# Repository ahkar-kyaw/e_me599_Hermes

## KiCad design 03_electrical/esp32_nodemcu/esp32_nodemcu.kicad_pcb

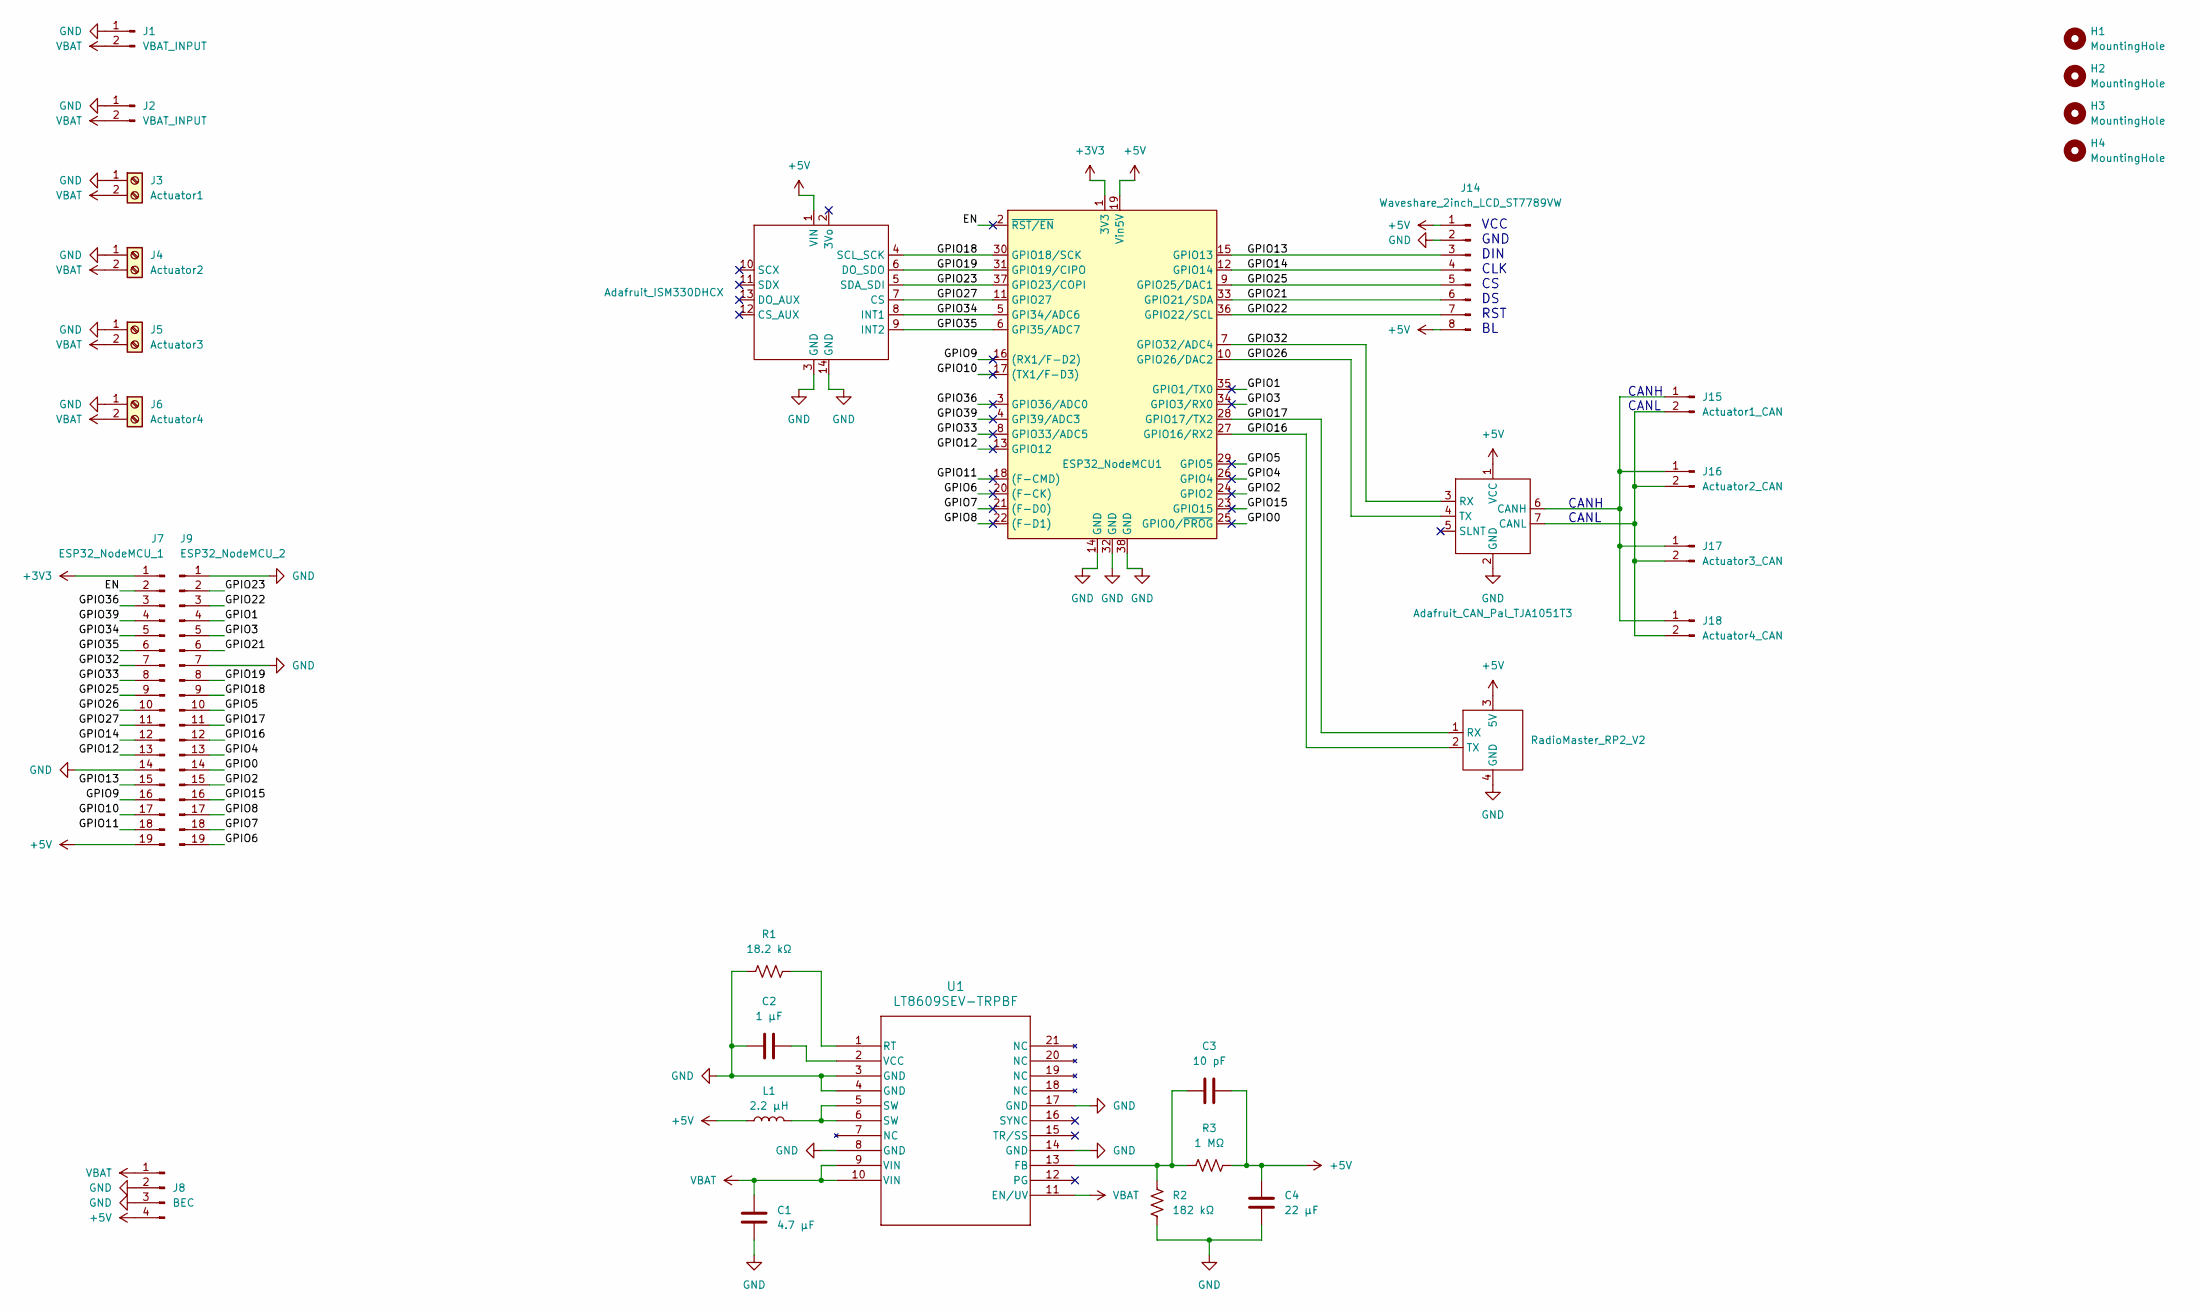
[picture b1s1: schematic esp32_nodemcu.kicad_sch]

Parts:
A1: Adafruit_ISM330DHCX
A2: Adafruit_CAN_Pal_TJA1051T3
A3: RadioMaster_RP2_V2
C1: 4.7 μF; C_1206_3216Metric_Pad1.33x1.80mm_HandSolder
C2: 1 μF; C_0603_1608Metric_Pad1.08x0.95mm_HandSolder
C3: 10 pF; C_0603_1608Metric_Pad1.08x0.95mm_HandSolder
C4: 22 μF; C_1206_3216Metric_Pad1.33x1.80mm_HandSolder
H1, H2, H3, H4: MountingHole; MountingHole_3.5mm_Pad_TopBottom
J1, J2: VBAT_INPUT; 12GaugePower
J3: Actuator1; TerminalBlock_Phoenix_MKDS-1,5-2-5.08_1x02_P5.08mm_Horizont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
J4: Actuator2; TerminalBlock_Phoenix_MKDS-1,5-2-5.08_1x02_P5.08mm_Horizont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
J5: Actuator3; TerminalBlock_Phoenix_MKDS-1,5-2-5.08_1x02_P5.08mm_Horizont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
J6: Actuator4; TerminalBlock_Phoenix_MKDS-1,5-2-5.08_1x02_P5.08mm_Horizont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
J7: ESP32_NodeMCU_1; PinHeader_1x19_P2.54mm_Vertical
J8: BEC; PinHeader_1x04_P2.54mm_Vertical
J9: ESP32_NodeMCU_2; PinHeader_1x19_P2.54mm_Vertical
J14: Waveshare_2inch_LCD_ST7789VW; JST_PH_B8B-PH-K_1x08_P2.00mm_Vertical
J15: Actuator1_CAN; PinHeader_1x02_P2.54mm_Vertical
J16: Actuator2_CAN; PinHeader_1x02_P2.54mm_Vertical
J17: Actuator3_CAN; PinHeader_1x02_P2.54mm_Vertical
J18: Actuator4_CAN; PinHeader_1x02_P2.54mm_Vertical
L1: 2.2 μH; L_Coilcraft_XxL4020
R1: 18.2 kΩ; R_0603_1608Metric_Pad0.98x0.95mm_HandSolder
R2: 182 kΩ; R_0603_1608Metric_Pad0.98x0.95mm_HandSolder
R3: 1 MΩ; R_0603_1608Metric_Pad0.98x0.95mm_HandSolder
U1: LT8609SEV-TRPBF; 05-08-1516_ADI
U2: ESP32_NodeMCU1; ESP32_NodeMCU

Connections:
+3V3: J7.1, U2.1 (3V3)
+5V: A1.1 (VIN), A2.1 (VCC), A3.3 (5V), C3.2, C4.1, J7.19, J8.4, J14.1, J14.8, L1.1, R3.1, U2.19 (Vin5V)
/EN: J7.2, U2.2 (~RST/EN)
/GPIO0: J9.14, U2.25 (GPIO0/~PROG)
/GPIO1: J9.4, U2.35 (GPIO1/TX0)
/GPIO2: J9.15, U2.24 (GPIO2)
/GPIO3: J9.5, U2.34 (GPIO3/RX0)
/GPIO4: J9.13, U2.26 (GPIO4)
/GPIO5: J9.10, U2.29 (GPIO5)
/GPIO6: J9.19, U2.20 ((F-CK))
/GPIO7: J9.18, U2.21 ((F-D0))
/GPIO8: J9.17, U2.22 ((F-D1))
/GPIO9: J7.16, U2.16 ((RX1/F-D2))
/GPIO10: J7.17, U2.17 ((TX1/F-D3))
/GPIO11: J7.18, U2.18 ((F-CMD))
/GPIO12: J7.13, U2.13 (GPIO12)
/GPIO13: J7.15, J14.3, U2.15 (GPIO13)
/GPIO14: J7.12, J14.4, U2.12 (GPIO14)
/GPIO15: J9.16, U2.23 (GPIO15)
/GPIO16: A3.2 (TX), J9.12, U2.27 (GPIO16/RX2)
/GPIO17: A3.1 (RX), J9.11, U2.28 (GPIO17/TX2)
/GPIO18: A1.4 (SCL_SCK), J9.9, U2.30 (GPIO18/SCK)
/GPIO19: A1.6 (DO_SDO), J9.8, U2.31 (GPIO19/CIPO)
/GPIO21: J9.6, J14.6, U2.33 (GPIO21/SDA)
/GPIO22: J9.3, J14.7, U2.36 (GPIO22/SCL)
/GPIO23: A1.5 (SDA_SDI), J9.2, U2.37 (GPIO23/COPI)
/GPIO25: J7.9, J14.5, U2.9 (GPIO25/DAC1)
/GPIO26: A2.4 (TX), J7.10, U2.10 (GPIO26/DAC2)
/GPIO27: A1.7 (CS), J7.11, U2.11 (GPIO27)
/GPIO32: A2.3 (RX), J7.7, U2.7 (GPIO32/ADC4)
/GPIO33: J7.8, U2.8 (GPIO33/ADC5)
/GPIO34: A1.8 (INT1), J7.5, U2.5 (GPI34/ADC6)
/GPIO35: A1.9 (INT2), J7.6, U2.6 (GPI35/ADC7)
/GPIO36: J7.3, U2.3 (GPIO36/ADC0)
/GPIO39: J7.4, U2.4 (GPI39/ADC3)
GND: A1.3 (GND), A1.14 (GND), A2.2 (GND), A3.4 (GND), C1.2, C2.1, C4.2, J1.1, J2.1, J3.1, J4.1, J5.1, J6.1, J7.14, J8.2, J8.3, J9.1, J9.7, J14.2, R1.1, R2.1, U1.3 (GND), U1.4 (GND), U1.8 (GND), U1.14 (GND), U1.17 (GND), U2.14 (GND), U2.32 (GND), U2.38 (GND)
unnamed: A2.6 (CANH), J15.1, J16.1, J17.1, J18.1
unnamed: A2.7 (CANL), J15.2, J16.2, J17.2, J18.2
unnamed: L1.2, U1.5 (SW), U1.6 (SW)
unnamed: C3.1, R2.2, R3.2, U1.13 (FB)
unnamed: R1.2, U1.1 (RT)
unnamed: C2.2, U1.2 (VCC)
VBAT: C1.1, J1.2, J2.2, J3.2, J4.2, J5.2, J6.2, J8.1, U1.9 (VIN), U1.10 (VIN), U1.11 (EN/UV)

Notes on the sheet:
CANH CANL
VCC GND DIN CLK CS DS RST BL

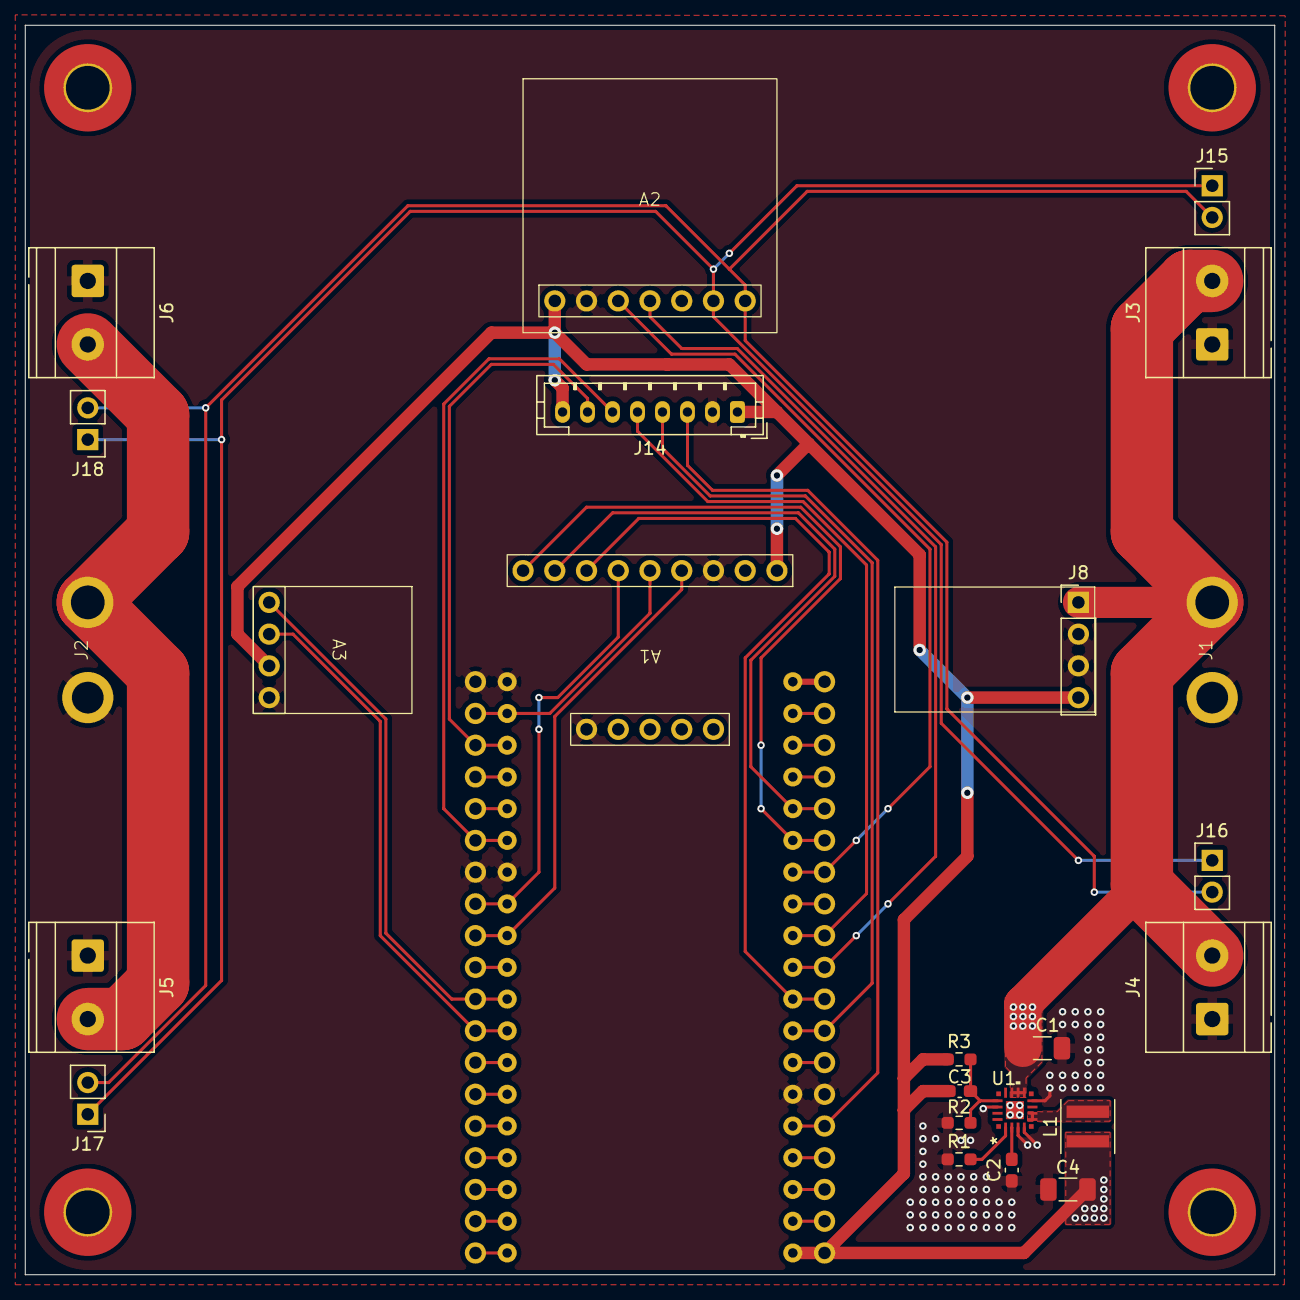
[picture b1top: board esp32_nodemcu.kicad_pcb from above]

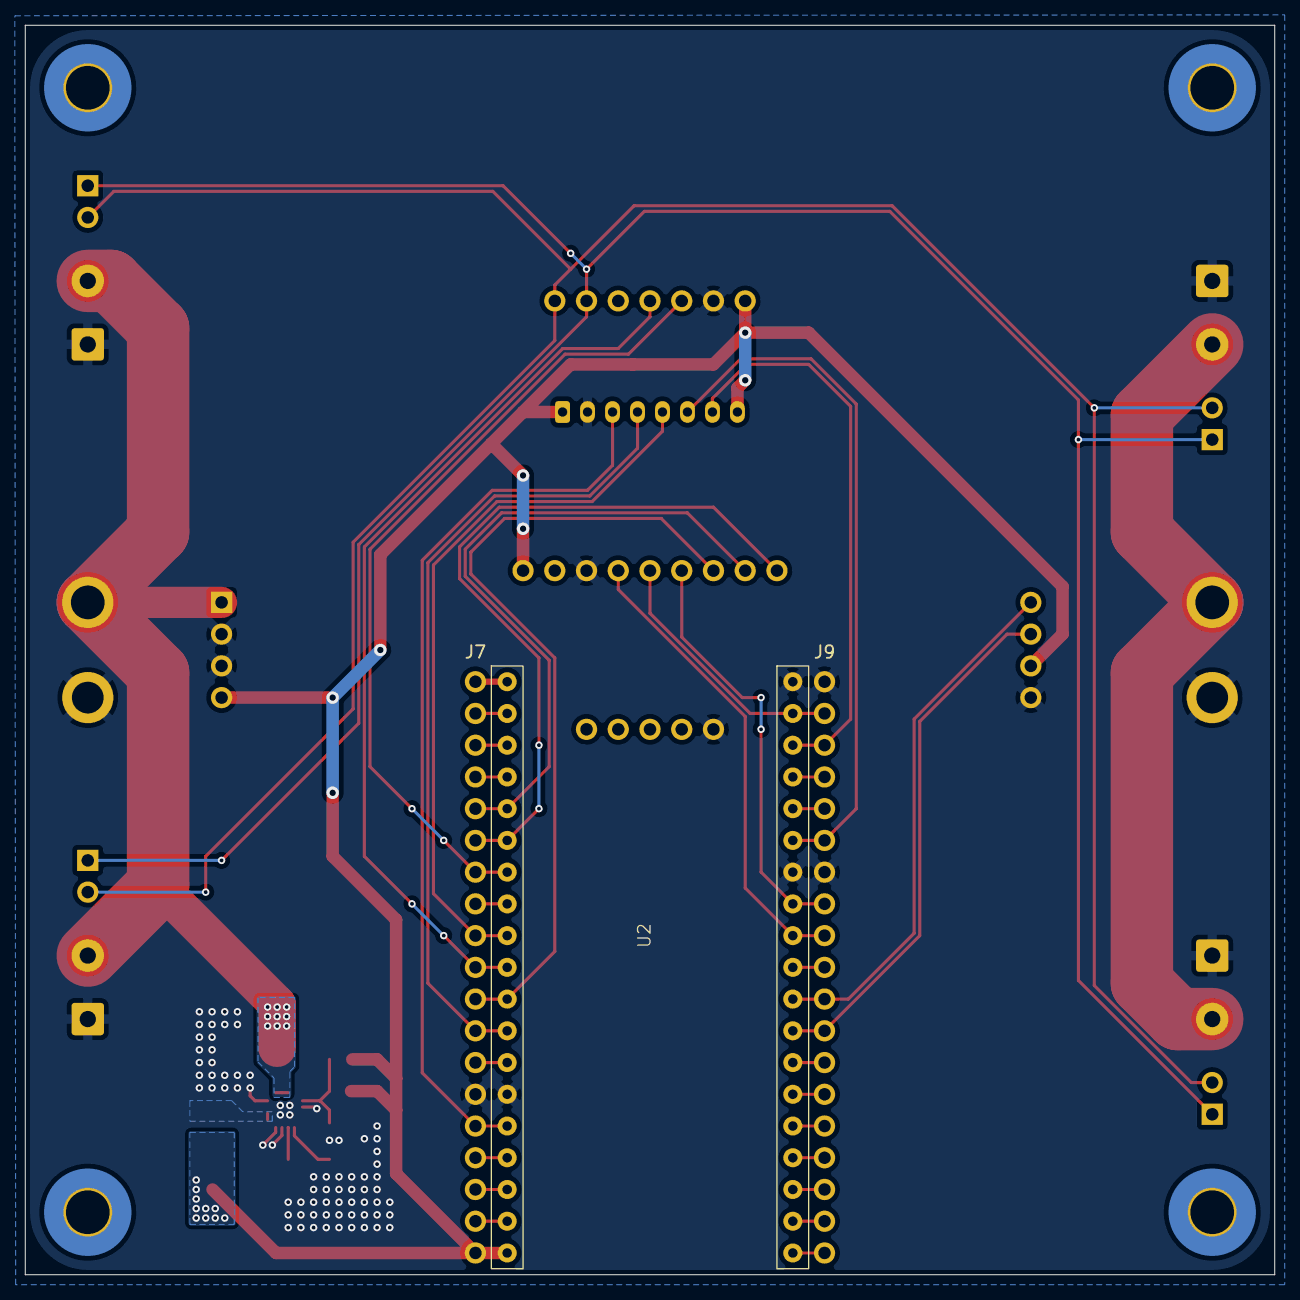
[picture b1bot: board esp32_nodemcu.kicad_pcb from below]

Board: 2 copper layers, 100.0 x 100.0 mm, 31 parts (3 on the bottom side), 43 nets.
